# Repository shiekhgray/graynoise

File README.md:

# graynoise
A place for my modular synthesizer designs. Generally openable in [kicad](https://kicad.org/). Or, if you trust me, ship the zipped gerber directories to your favorite PCB house. If you don't have a favorite, I can recommend PCBWay. Parts are generally available from either Tayda or Mouser.

Each directory should be a module, with two (or more) kicad projects. One (or more) should be the actual schematic and logic board(s), the other a faceplate.

## 4mixer
A small, 4hp, 4 channel mono mixer for Eurorack in kicad

## Offset Attenuverter
A 4hp dual attenuverter with offset function, useful for sidechain compression, FM and AM intensity control, and other CV management

## Avalanche
A 4hp? dingus for making white noise by running a zener diode in reverse avalanche mode

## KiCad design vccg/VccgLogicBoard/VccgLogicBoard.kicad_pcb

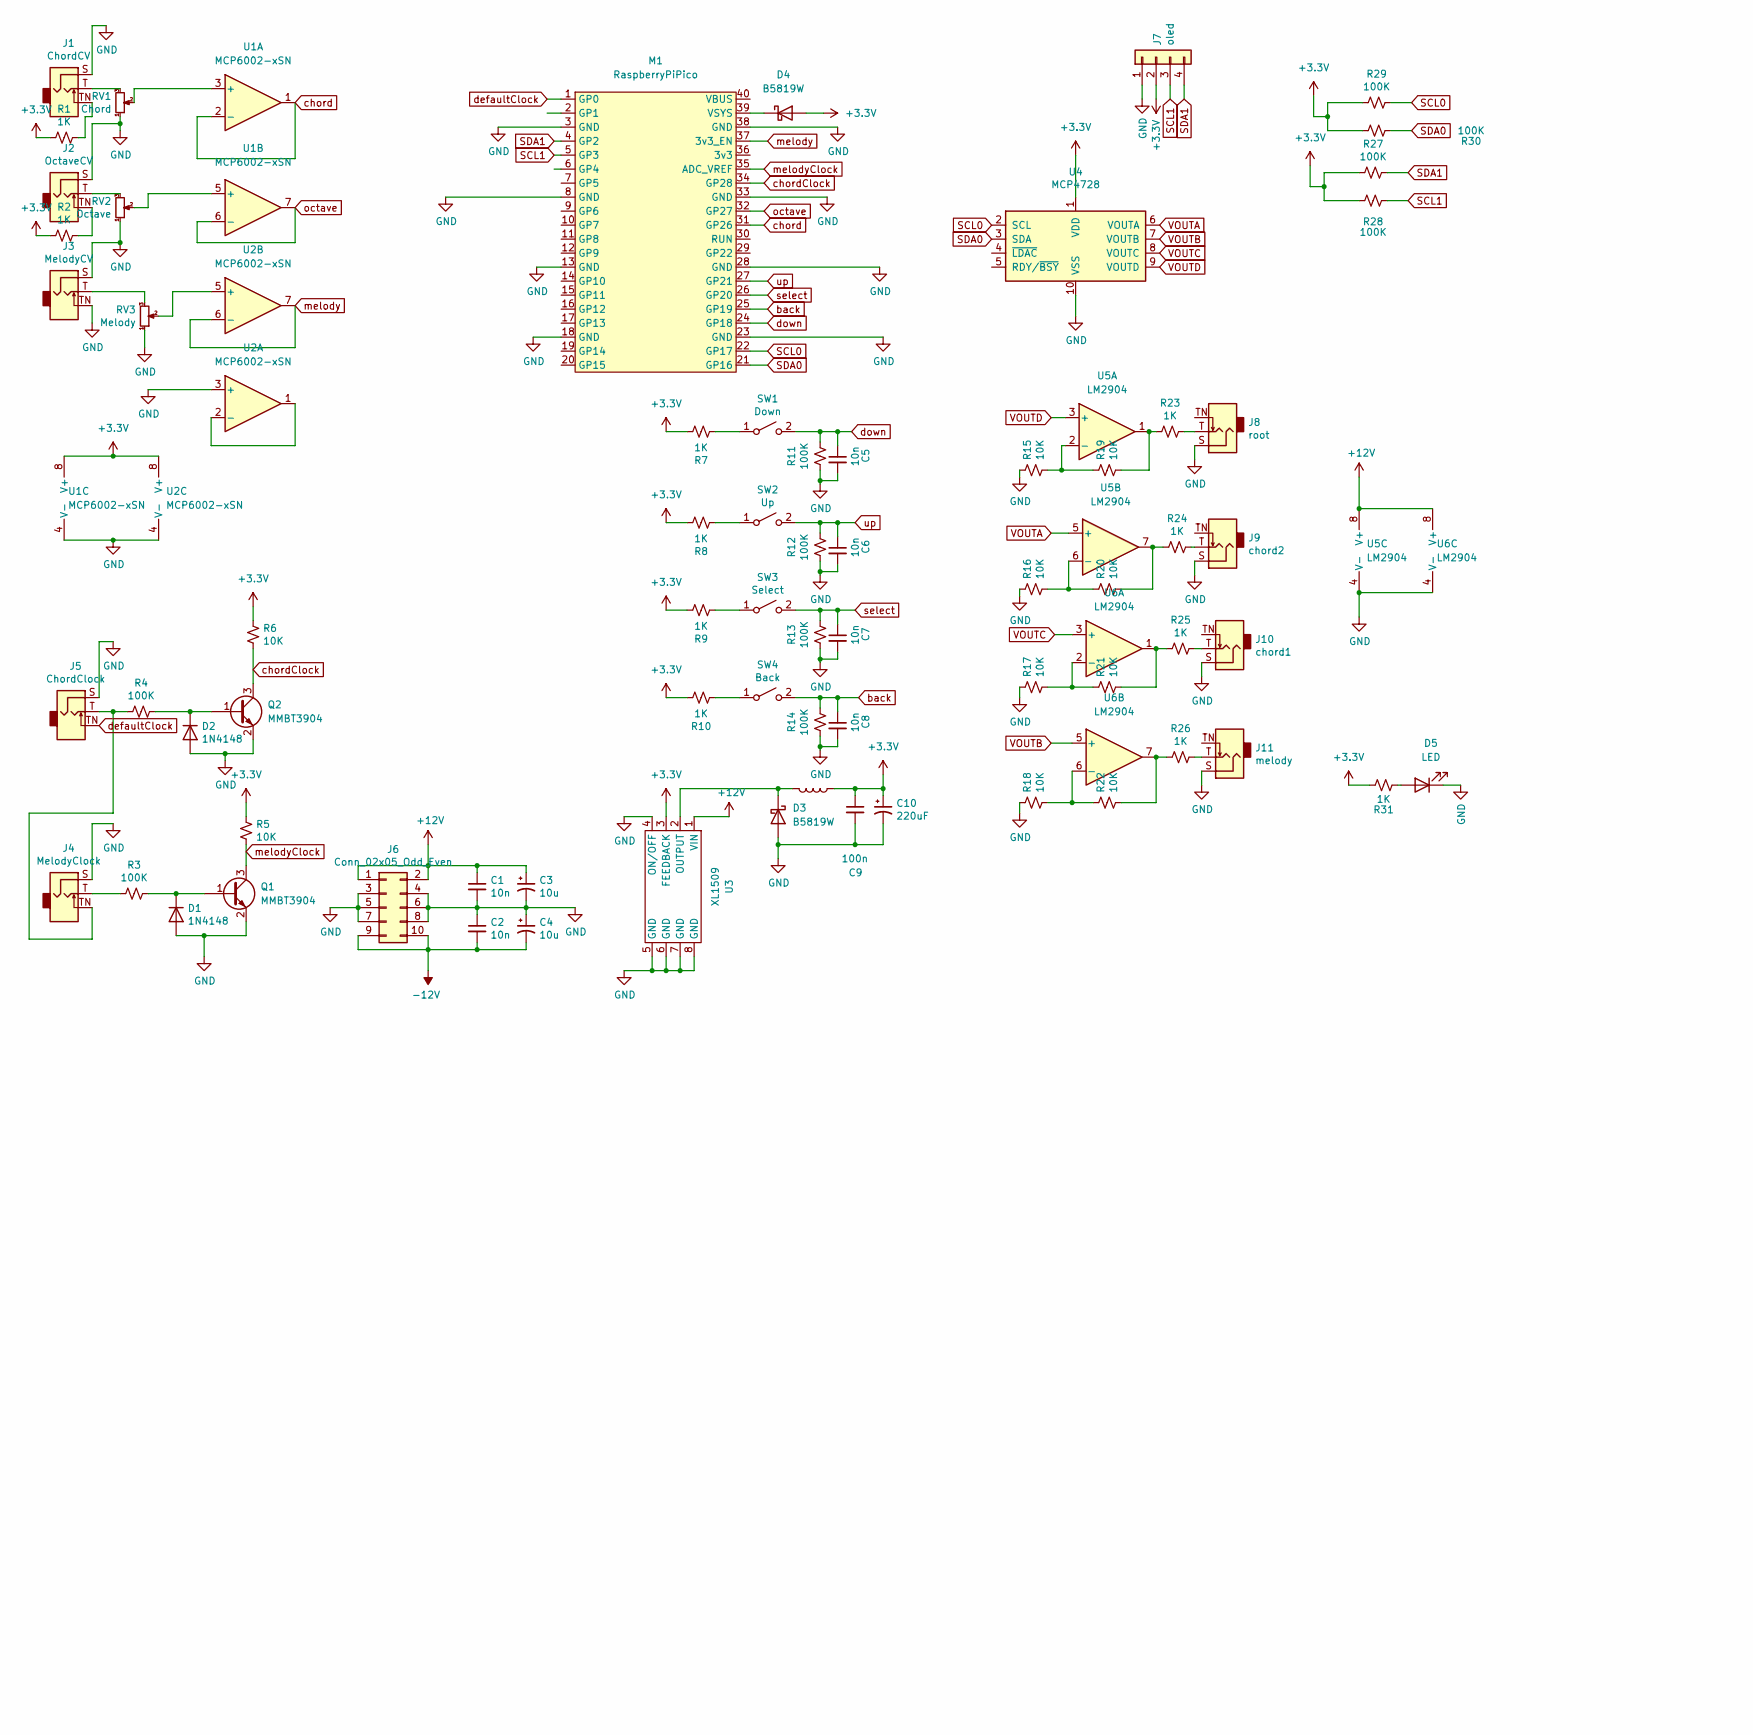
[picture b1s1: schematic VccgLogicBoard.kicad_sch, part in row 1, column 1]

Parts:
C1, C2, C5, C6, C7, C8: 10n; C_0603_1608Metric
C3, C4: 10u; C_0805_2012Metric
C9: 100n; C_0603_1608Metric
C10: 220uF; CP_Elec_6.3x7.7
D1, D2: 1N4148; D_SOD-123
D3, D4: B5819W; D_SOD-123
D5: LED; D_0603_1608Metric
J1: ChordCV; Jack_3.5mm_QingPu_WQP-PJ398SM_Vertical_CircularHoles
J2: OctaveCV; Jack_3.5mm_QingPu_WQP-PJ398SM_Vertical_CircularHoles
J3: MelodyCV; Jack_3.5mm_QingPu_WQP-PJ398SM_Vertical_CircularHoles
J4: MelodyClock; Jack_3.5mm_QingPu_WQP-PJ398SM_Vertical_CircularHoles
J5: ChordClock; Jack_3.5mm_QingPu_WQP-PJ398SM_Vertical_CircularHoles
J6: Conn_02x05_Odd_Even; PinHeader_2x05_P2.54mm_Vertical
J7: oled; PinSocket_1x04_P2.54mm_Vertical
J8: root; Jack_3.5mm_QingPu_WQP-PJ398SM_Vertical_CircularHoles
J9: chord2; Jack_3.5mm_QingPu_WQP-PJ398SM_Vertical_CircularHoles
J10: chord1; Jack_3.5mm_QingPu_WQP-PJ398SM_Vertical_CircularHoles
J11: melody; Jack_3.5mm_QingPu_WQP-PJ398SM_Vertical_CircularHoles
L1: 68uh 2A; Inductor_SMD-CY75-68uh
M1: RaspberryPiPico; Raspberry_Pi_Pico
Q1, Q2: MMBT3904; SOT-23
R1, R2, R7, R8, R9, R10, R23, R24, R25, R26, R31: 1K; R_0603_1608Metric
R3, R4, R11, R12, R13, R14, R27, R28, R29, R30: 100K; R_0603_1608Metric
R5, R6, R15, R16, R17, R18, R19, R20, R21, R22: 10K; R_0603_1608Metric
RV1: Chord; Potentiometer_Alpha_RD901F-40-00D_Single_Vertical_CircularH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
RV2: Octave; Potentiometer_Alpha_RD901F-40-00D_Single_Vertical_CircularH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
RV3: Melody; Potentiometer_Alpha_RD901F-40-00D_Single_Vertical_CircularH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
SW1: Down; SW_PUSH_6mm_H13mm
SW2: Up; SW_PUSH_6mm_H13mm
SW3: Select; SW_PUSH_6mm_H13mm
SW4: Back; SW_PUSH_6mm_H13mm
U1, U2: MCP6002-xSN; SOIC-8_3.9x4.9mm_P1.27mm
U3: XL1509; SOIC-8_3.9x4.9mm_P1.27mm
U4: MCP4728; MSOP-10_3x3mm_P0.5mm
U5, U6: LM2904; SOIC-8_3.9x4.9mm_P1.27mm

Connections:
+3V3: C9.1, C10.1, D4.2 (A), J7.2, L1.1, R1.2, R2.2, R5.2, R6.2, R7.1, R8.1, R9.1, R10.1, R27.2, R28.2, R29.2, R30.2, R31.2, U1.8 (V+), U2.8 (V+), U3.3 (FEEDBACK), U4.1 (VDD)
+12V: C1.1, C3.1, J6.1, J6.2, U3.1 (VIN), U5.8 (V+), U6.8 (V+)
-12V: C2.2, C4.2, J6.9, J6.10
GND: C1.2, C2.1, C3.2, C4.1, C5.2, C6.2, C7.2, C8.2, C9.2, C10.2, D1.2 (A), D2.2 (A), D3.2 (A), D5.1 (K), J1.S, J2.S, J3.S, J3.TN, J4.S, J5.S, J6.3, J6.4, J6.5, J6.6, J6.7, J6.8, J7.1, J8.S, J9.S, J10.S, J11.S, M1.3 (GND), M1.8 (GND), M1.13 (GND), M1.18 (GND), M1.23 (GND), M1.28 (GND), M1.33 (GND), M1.38 (GND), Q1.2 (E), Q2.2 (E), R11.2, R12.2, R13.2, R14.2, R15.2, R16.2, R17.2, R18.2, RV1.1, RV2.1, RV3.1, U1.4 (V-), U2.3 (+), U2.4 (V-), U3.4 (ON/OFF), U3.5 (GND), U3.6 (GND), U3.7 (GND), U3.8 (GND), U4.10 (VSS), U5.4 (V-), U6.4 (V-)
unnamed: D1.1 (K), Q1.1 (B), R3.1
unnamed: D2.1 (K), Q2.1 (B), R4.1
unnamed: D3.1 (K), L1.2, U3.2 (OUTPUT)
unnamed: D4.1 (K), M1.39 (VSYS)
unnamed: D5.2 (A), R31.1
unnamed: J1.T, RV1.3
unnamed: J1.TN, R1.1
unnamed: J2.T, RV2.3
unnamed: J2.TN, R2.1
unnamed: J3.T, RV3.3
unnamed: J4.T, R3.2
unnamed: J4.TN, J5.T, R4.2
unnamed: J8.T, R23.1
unnamed: J9.T, R24.1
unnamed: J10.T, R25.1
unnamed: J11.T, R26.1
unnamed: R7.2, SW1.1 (A)
unnamed: R8.2, SW2.1 (A)
unnamed: R9.2, SW3.1 (A)
unnamed: R10.2, SW4.1 (A)
unnamed: R15.1, R19.2, U5.2 (-)
unnamed: R16.1, R20.2, U5.6 (-)
unnamed: R17.1, R21.2, U6.2 (-)
unnamed: R18.1, R22.2, U6.6 (-)
unnamed: R19.1, R23.2, U5.1
unnamed: R20.1, R24.2, U5.7
unnamed: R21.1, R25.2, U6.1
unnamed: R22.1, R26.2, U6.7
unnamed: RV1.2, U1.3 (+)
unnamed: RV2.2, U1.5 (+)
unnamed: RV3.2, U2.5 (+)
unnamed: U2.1, U2.2 (-)
SCL0: M1.22 (GP17), R29.1, U4.2 (SCL)
SCL1: J7.3, M1.5 (GP3), R28.1
SDA0: M1.21 (GP16), R30.1, U4.3 (SDA)
SDA1: J7.4, M1.4 (GP2), R27.1
VOUTA: U4.6 (VOUTA), U5.5 (+)
VOUTB: U4.7 (VOUTB), U6.5 (+)
VOUTC: U4.8 (VOUTC), U6.3 (+)
VOUTD: U4.9 (VOUTD), U5.3 (+)
back: C8.1, M1.25 (GP19), R14.1, SW4.2 (B)
chord: M1.31 (GP26), U1.1, U1.2 (-)
chordClock: M1.34 (GP28), Q2.3 (C), R6.1
defaultClock: J5.TN, M1.1 (GP0)
down: C5.1, M1.24 (GP18), R11.1, SW1.2 (B)
melody: M1.37 (3v3_EN), U2.6 (-), U2.7
melodyClock: M1.35 (ADC_VREF), Q1.3 (C), R5.1
octave: M1.32 (GP27), U1.6 (-), U1.7
select: C7.1, M1.26 (GP20), R13.1, SW3.2 (B)
up: C6.1, M1.27 (GP21), R12.1, SW2.2 (B)

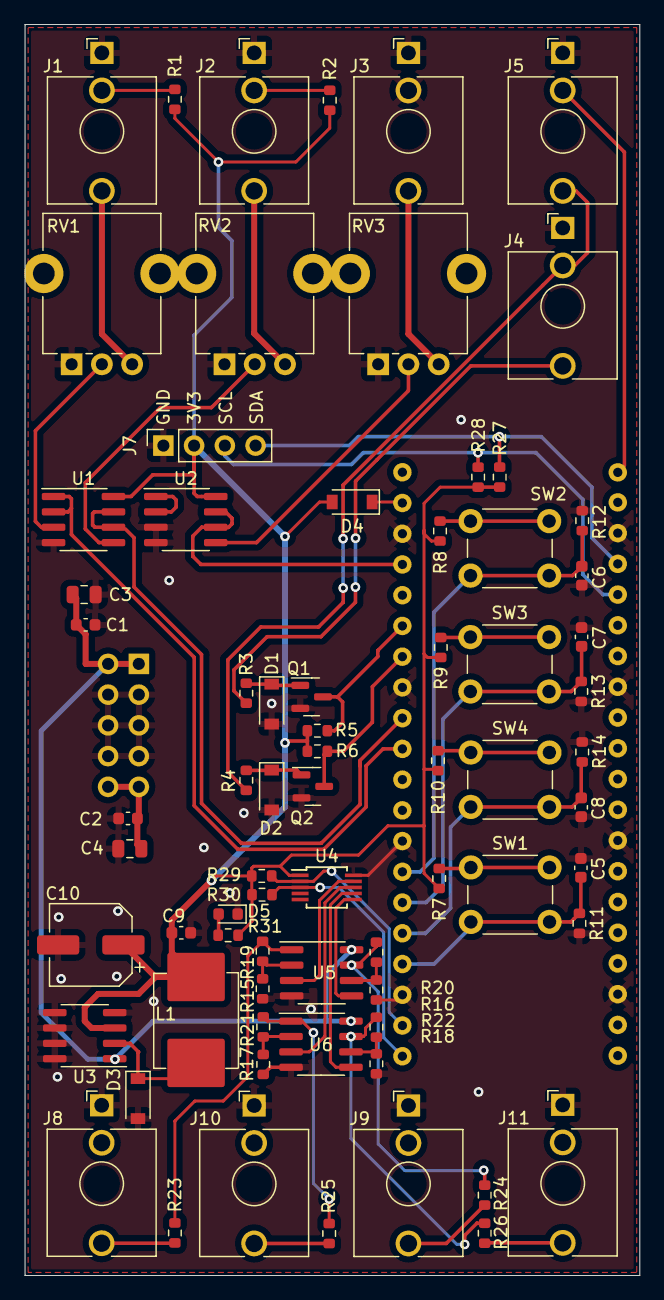
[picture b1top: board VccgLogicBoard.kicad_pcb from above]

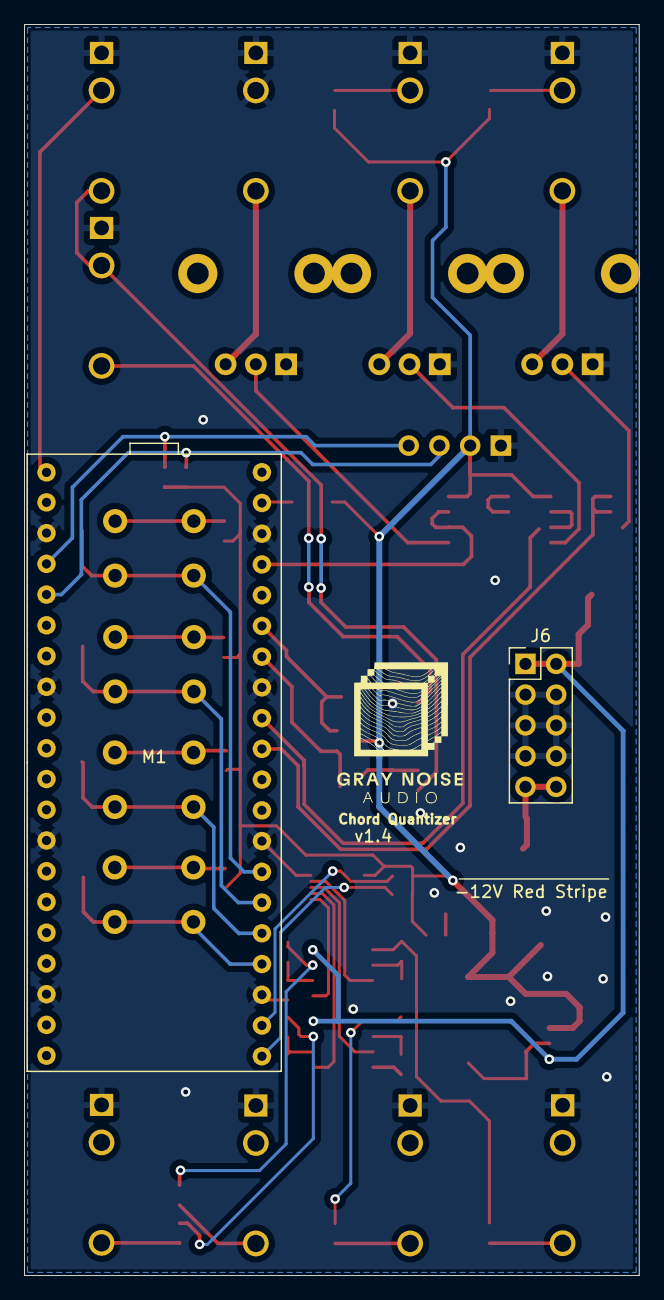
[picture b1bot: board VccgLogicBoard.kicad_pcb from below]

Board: 2 copper layers, 50.8 x 103.4 mm, 74 parts (2 on the bottom side), 54 nets.

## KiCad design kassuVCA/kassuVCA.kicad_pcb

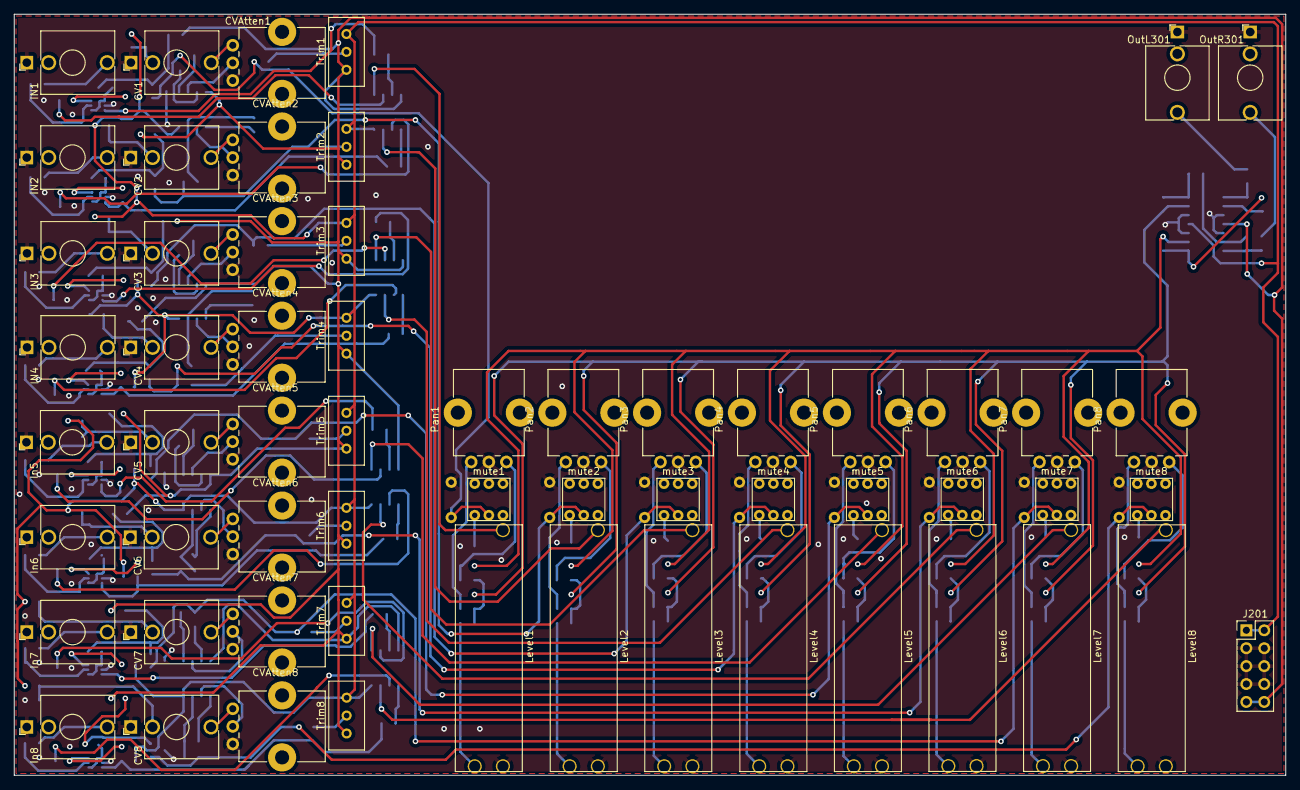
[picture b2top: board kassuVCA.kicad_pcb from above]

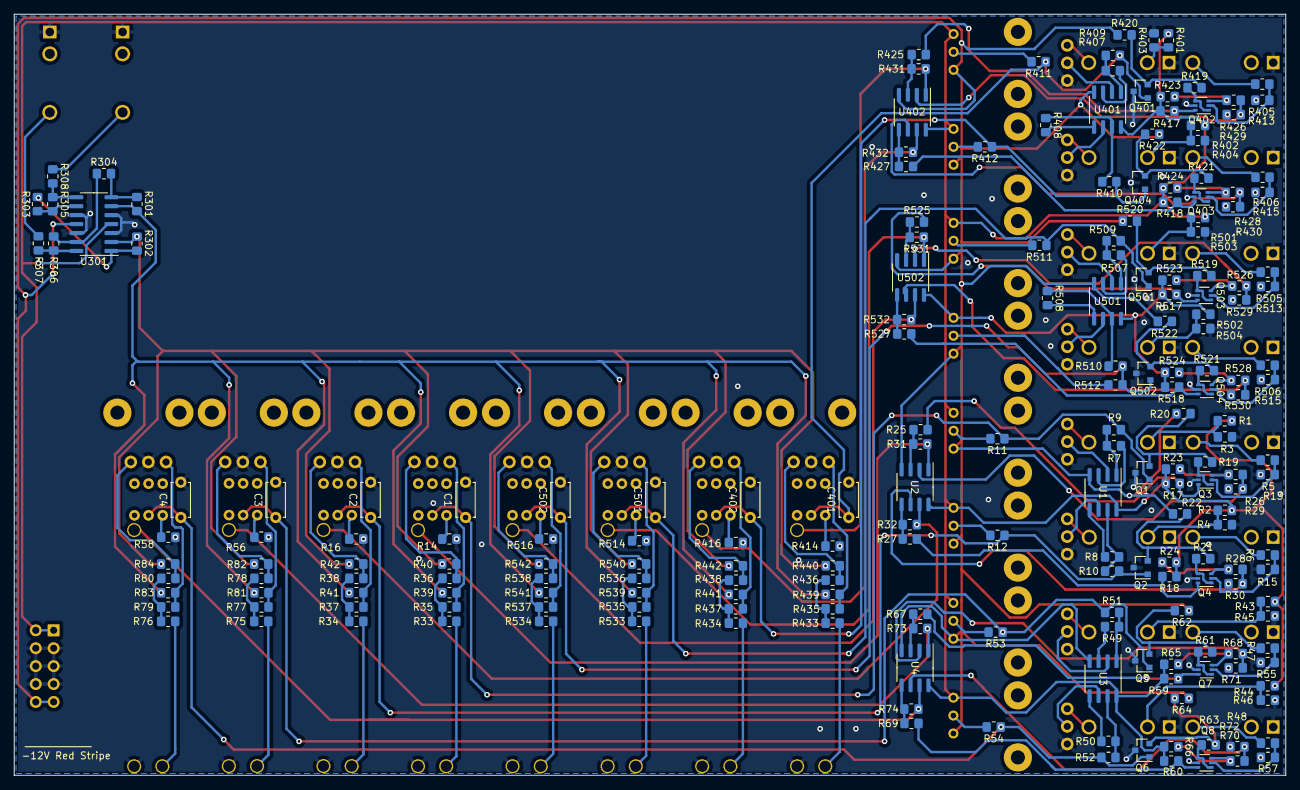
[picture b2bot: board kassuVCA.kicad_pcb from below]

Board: 2 copper layers, 180.3 x 107.9 mm, 268 parts (209 on the bottom side), 181 nets.

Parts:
C1, C2, C3, C4, C401, C402, C501, C502: C; C_Disc_D4.7mm_W2.5mm_P5.00mm
CV1, CV3, CV5, CV6, CV7, CV8: AudioJack2_SwitchT; Jack_3.5mm_QingPu_WQP-PJ398SM_Vertical_CircularHoles
CV2, CV4: AudioJack2_Switch; Jack_3.5mm_QingPu_WQP-PJ398SM_Vertical_CircularHoles
CVAtten1, CVAtten2, CVAtten3, CVAtten4, CVAtten5, CVAtten6, CVAtten7, CVAtten8: 100K; Potentiometer_Alps_RK09K_Single_Vertical
IN1, IN2, IN3, IN4: AudioJack2_SwitchT; Jack_3.5mm_QingPu_WQP-PJ398SM_Vertical_CircularHoles
In5, In6, In7, In8: AudioJack2_SwitchT; Jack_3.5mm_QingPu_WQP-PJ398SM_Vertical_CircularHoles
J201: Conn_02x05_Odd_Even; PinHeader_2x05_P2.54mm_Vertical
Level1, Level2, Level3, Level4, Level5, Level6, Level7, Level8: 100K; A-1623_SlidePot
OutL301: AudioJack2_SwitchT; Jack_3.5mm_QingPu_WQP-PJ398SM_Vertical_CircularHoles
OutR301: AudioJack2_SwitchT; Jack_3.5mm_QingPu_WQP-PJ398SM_Vertical_CircularHoles
Pan1, Pan2, Pan3, Pan4, Pan5, Pan6, Pan7, Pan8: 100K; Potentiometer_Alps_RK09K_Single_Vertical
Q1, Q2, Q5, Q6, Q401, Q404, Q501, Q502: MMBT3904; SOT-23
Q3, Q4, Q7, Q8, Q402, Q403, Q503, Q504: MBT3904DW1; SOT-363_SC-70-6
R1, R2, R5, R6, R29, R30, R31, R32, R33, R34, R43, R44, R47, R48, R71, R72, R73, R74, R75, R76, R401, R402, R405, R406, R429, R430, R431, R432, R433, R434, R501, R502, R505, R506, R529, R530, R531, R532, R533, R534: 220K; R_0805_2012Metric_Pad1.20x1.40mm_HandSolder
R3, R4, R45, R46, R305, R306, R403, R404, R503, R504: 100K; R_0805_2012Metric_Pad1.20x1.40mm_HandSolder
R7, R8, R49, R50, R407, R408, R507, R508: 47K; R_0805_2012Metric_Pad1.20x1.40mm_HandSolder
R9, R10, R11, R12, R19, R21, R35, R36, R37, R38, R39, R40, R41, R42, R51, R52, R53, R54, R61, R63, R77, R78, R79, R80, R81, R82, R83, R84, R409, R410, R411, R412, R419, R421, R435, R436, R437, R438, R439, R440, R441, R442, R509, R510, R511, R512, R519, R521, R535, R536, R537, R538, R539, R540, R541, R542: 22K; R_0805_2012Metric_Pad1.20x1.40mm_HandSolder
R13, R14, R15, R16, R55, R56, R57, R58, R307, R308, R413, R414, R415, R416, R513, R514, R515, R516: 1K; R_0805_2012Metric_Pad1.20x1.40mm_HandSolder
R17, R18, R20, R22, R23, R24, R25, R26, R27, R28, R59, R60, R62, R64, R65, R66, R67, R68, R69, R70, R417, R418, R420, R422, R423, R424, R425, R426, R427, R428, R517, R518, R520, R522, R523, R524, R525, R526, R527, R528: 10K; R_0805_2012Metric_Pad1.20x1.40mm_HandSolder
R301, R302: 39K; R_0805_2012Metric_Pad1.20x1.40mm_HandSolder
R303, R304: 2K; R_0805_2012Metric_Pad1.20x1.40mm_HandSolder
Trim1, Trim2, Trim3, Trim4, Trim5, Trim6, Trim7, Trim8: 100K; Potentiometer_Bourns_3296W_Vertical
U1, U2, U3, U4, U401, U402, U501, U502: TL072; SOIC-8_3.9x4.9mm_P1.27mm
U301: TL074; SOIC-14_3.9x8.7mm_P1.27mm
mute1, mute2, mute3, mute4, mute6, mute8: SW_DPDT_x2; A-330-6mm-dpdt
mute5: mute5; A-330-6mm-dpdt
mute7: mute7; A-330-6mm-dpdt

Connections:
+12V: J201.1, J201.2, R1.1, R2.1, R17.1, R18.1, R23.1, R24.1, R43.1, R44.1, R59.1, R60.1, R65.1, R66.1, R401.1, R402.1, R417.1, R418.1, R423.1, R424.1, R501.1, R502.1, R517.1, R518.1, R523.1, R524.1, Trim1.1, Trim2.1, Trim3.1, Trim4.1, Trim5.1, Trim6.1, Trim7.1, Trim8.1, U1.8 (V+), U2.8 (V+), U3.8 (V+), U4.8 (V+), U301.4 (V+), U401.8 (V+), U402.8 (V+), U501.8 (V+), U502.8 (V+)
-12V: J201.9, J201.10, R20.1, R22.1, R62.1, R64.1, R420.1, R422.1, R520.1, R522.1, Trim1.3, Trim2.3, Trim3.3, Trim4.3, Trim5.3, Trim6.3, Trim7.3, Trim8.3, U1.4 (V-), U2.4 (V-), U3.4 (V-), U4.4 (V-), U301.11 (V-), U401.4 (V-), U402.4 (V-), U501.4 (V-), U502.4 (V-)
GND: C1.2, C2.2, C3.2, C4.2, C401.2, C402.2, C501.2, C502.2, CV1.S, CV2.S, CV3.S, CV4.S, CV5.S, CV6.S, CV7.S, CV8.S, CVAtten1.1, CVAtten2.1, CVAtten3.1, CVAtten4.1, CVAtten5.1, CVAtten6.1, CVAtten7.1, CVAtten8.1, IN1.S, IN2.S, IN3.S, IN4.S, In5.S, In6.S, In7.S, In8.S, J201.3, J201.4, J201.5, J201.6, J201.7, J201.8, Level1.1, Level2.1, Level3.1, Level4.1, Level5.1, Level6.1, Level7.1, Level8.1, OutL301.S, OutR301.S, Pan1.2, Pan2.2, Pan3.2, Pan4.2, Pan5.2, Pan6.2, Pan7.2, Pan8.2, Q1.3 (C), Q2.3 (C), Q3.5 (B2), Q4.5 (B2), Q5.3 (C), Q6.3 (C), Q7.5 (B2), Q8.5 (B2), Q401.3 (C), Q402.5 (B2), Q403.5 (B2), Q404.3 (C), Q501.3 (C), Q502.3 (C), Q503.5 (B2), Q504.5 (B2), R3.2, R4.2, R13.1, R14.1, R15.1, R16.1, R29.1, R30.1, R45.2, R46.2, R55.1, R56.1, R57.1, R58.1, R71.1, R72.1, R403.2, R404.2, R413.1, R414.1, R415.1, R416.1, R429.1, R430.1, R503.2, R504.2, R513.1, R514.1, R515.1, R516.1, R529.1, R530.1, U301.3 (+), U301.5 (+), U301.10 (+), U301.12 (+)
Level1L: R40.2, R42.2, R82.2, R84.2, R302.2, R440.2, R442.2, R540.2, R542.2, U301.2 (-)
Level1R: R39.2, R41.2, R81.2, R83.2, R301.2, R439.2, R441.2, R539.2, R541.2, U301.6 (-)
unnamed: C1.1, Q1.1 (B), R9.1, R11.1, mute5.2 (B)
unnamed: C2.1, Q2.1 (B), R10.1, R12.1, mute6.2 (B)
unnamed: C3.1, Q5.1 (B), R51.1, R53.1, mute7.2 (B)
unnamed: C4.1, Q6.1 (B), R52.1, R54.1, mute8.2 (B)
unnamed: C401.1, Q401.1 (B), R409.1, R411.1, mute1.2 (B)
unnamed: C402.1, Q404.1 (B), R410.1, R412.1, mute2.2 (B)
unnamed: C501.1, Q501.1 (B), R509.1, R511.1, mute3.2 (B)
unnamed: C502.1, Q502.1 (B), R510.1, R512.1, mute4.2 (B)
unnamed: CV1.T, CVAtten1.3
unnamed: CV1.TN, R401.2, R403.1
unnamed: CV2.T, CVAtten2.3
unnamed: CV2.TN, R402.2, R404.1
unnamed: CV3.T, CVAtten3.3
unnamed: CV3.TN, R501.2, R503.1
unnamed: CV4.T, CVAtten4.3
unnamed: CV4.TN, R502.2, R504.1
unnamed: CV5.T, CVAtten5.3
unnamed: CV5.TN, R1.2, R3.1
unnamed: CV6.T, CVAtten6.3
unnamed: CV6.TN, R2.2, R4.1
unnamed: CV7.T, CVAtten7.3
unnamed: CV7.TN, R43.2, R45.1
unnamed: CV8.T, CVAtten8.3
unnamed: CV8.TN, R44.2, R46.1
unnamed: CVAtten1.2, U401.2 (-)
unnamed: CVAtten2.2, U401.6 (-)
unnamed: CVAtten3.2, U501.2 (-)
unnamed: CVAtten4.2, U501.6 (-)
unnamed: CVAtten5.2, U1.2 (-)
unnamed: CVAtten6.2, U1.6 (-)
unnamed: CVAtten7.2, U3.2 (-)
unnamed: CVAtten8.2, U3.6 (-)
unnamed: IN1.T, R405.2
unnamed: IN2.T, R406.2
unnamed: IN3.T, R505.2
unnamed: IN4.T, R506.2
unnamed: In5.T, R5.2
unnamed: In6.T, R6.2
unnamed: In7.T, R47.2
unnamed: In8.T, R48.2
unnamed: Level1.2, R433.1
unnamed: Level1.3, R431.1, U402.1
unnamed: Level2.2, R434.1
unnamed: Level2.3, R432.1, U402.7
unnamed: Level3.2, R533.1
unnamed: Level3.3, R531.1, U502.1
unnamed: Level4.2, R534.1
unnamed: Level4.3, R532.1, U502.7
unnamed: Level5.2, R33.1
unnamed: Level5.3, R31.1, U2.1
unnamed: Level6.2, R34.1
unnamed: Level6.3, R32.1, U2.7
unnamed: Level7.2, R75.1
unnamed: Level7.3, R73.1, U4.1
unnamed: Level8.2, R76.1
unnamed: Level8.3, R74.1, U4.7
unnamed: OutL301.T, R308.1
unnamed: OutR301.T, R307.1
unnamed: Pan1.1, R436.2, R440.1
unnamed: Pan1.3, R435.2, R439.1
unnamed: Pan2.1, R438.2, R442.1
unnamed: Pan2.3, R437.2, R441.1
unnamed: Pan3.1, R536.2, R540.1
unnamed: Pan3.3, R535.2, R539.1
unnamed: Pan4.1, R538.2, R542.1
unnamed: Pan4.3, R537.2, R541.1
unnamed: Pan5.1, R36.2, R40.1
unnamed: Pan5.3, R35.2, R39.1
unnamed: Pan6.1, R38.2, R42.1
unnamed: Pan6.3, R37.2, R41.1
unnamed: Pan7.1, R78.2, R82.1
unnamed: Pan7.3, R77.2, R81.1
unnamed: Pan8.1, R80.2, R84.1
unnamed: Pan8.3, R79.2, R83.1
unnamed: Q1.2 (E), R19.2, R20.2
unnamed: Q2.2 (E), R21.2, R22.2
unnamed: Q3.1 (E1), Q3.4 (E2), R19.1
unnamed: Q3.2 (B1), R5.1, R13.2
unnamed: Q3.3 (C2), R23.2, R26.2
unnamed: Q3.6 (C1), R17.2, R25.2
unnamed: Q4.1 (E1), Q4.4 (E2), R21.1
unnamed: Q4.2 (B1), R6.1, R15.2
unnamed: Q4.3 (C2), R24.2, R28.2
unnamed: Q4.6 (C1), R18.2, R27.2
unnamed: Q5.2 (E), R61.2, R62.2
unnamed: Q6.2 (E), R63.2, R64.2
unnamed: Q7.1 (E1), Q7.4 (E2), R61.1
unnamed: Q7.2 (B1), R47.1, R55.2
unnamed: Q7.3 (C2), R65.2, R68.2
unnamed: Q7.6 (C1), R59.2, R67.2
unnamed: Q8.1 (E1), Q8.4 (E2), R63.1
unnamed: Q8.2 (B1), R48.1, R57.2
unnamed: Q8.3 (C2), R66.2, R70.2
unnamed: Q8.6 (C1), R60.2, R69.2
unnamed: Q401.2 (E), R419.2, R420.2
unnamed: Q402.1 (E1), Q402.4 (E2), R419.1
unnamed: Q402.2 (B1), R405.1, R413.2
unnamed: Q402.3 (C2), R423.2, R426.2
unnamed: Q402.6 (C1), R417.2, R425.2
unnamed: Q403.1 (E1), Q403.4 (E2), R421.1
unnamed: Q403.2 (B1), R406.1, R415.2
unnamed: Q403.3 (C2), R424.2, R428.2
unnamed: Q403.6 (C1), R418.2, R427.2
unnamed: Q404.2 (E), R421.2, R422.2
unnamed: Q501.2 (E), R519.2, R520.2
unnamed: Q502.2 (E), R521.2, R522.2
unnamed: Q503.1 (E1), Q503.4 (E2), R519.1
unnamed: Q503.2 (B1), R505.1, R513.2
unnamed: Q503.3 (C2), R523.2, R526.2
unnamed: Q503.6 (C1), R517.2, R525.2
unnamed: Q504.1 (E1), Q504.4 (E2), R521.1
unnamed: Q504.2 (B1), R506.1, R515.2
unnamed: Q504.3 (C2), R524.2, R528.2
unnamed: Q504.6 (C1), R518.2, R527.2
unnamed: R7.1, R9.2, U1.1
unnamed: R7.2, U1.3 (+)
unnamed: R8.2, U1.5 (+)
unnamed: R8.1, R10.2, U1.7
unnamed: R11.2, Trim5.2
unnamed: R12.2, Trim6.2
unnamed: R14.2, mute5.1 (A)
unnamed: R16.2, mute6.1 (A)
unnamed: R25.1, R31.2, U2.3 (+)
unnamed: R26.1, R29.2, U2.2 (-)
unnamed: R27.1, R32.2, U2.5 (+)
unnamed: R28.1, R30.2, U2.6 (-)
unnamed: R33.2, R35.1, R36.1
unnamed: R34.2, R37.1, R38.1
unnamed: R49.1, R51.2, U3.1
unnamed: R49.2, U3.3 (+)
unnamed: R50.1, R52.2, U3.7
unnamed: R50.2, U3.5 (+)
unnamed: R53.2, Trim7.2
unnamed: R54.2, Trim8.2
unnamed: R56.2, mute7.1 (A)
unnamed: R58.2, mute8.1 (A)
unnamed: R67.1, R73.2, U4.3 (+)
unnamed: R68.1, R71.2, U4.2 (-)
unnamed: R69.1, R74.2, U4.5 (+)
unnamed: R70.1, R72.2, U4.6 (-)
unnamed: R75.2, R77.1, R78.1
unnamed: R76.2, R79.1, R80.1
unnamed: R301.1, R304.2, U301.7
unnamed: R302.1, R303.2, U301.1
unnamed: R303.1, R305.2, U301.9 (-)
unnamed: R304.1, R306.2, U301.13 (-)
unnamed: R305.1, R308.2, U301.8
unnamed: R306.1, R307.2, U301.14
unnamed: R407.1, R409.2, U401.1
unnamed: R407.2, U401.3 (+)
unnamed: R408.1, R410.2, U401.7
unnamed: R408.2, U401.5 (+)
unnamed: R411.2, Trim1.2
unnamed: R412.2, Trim2.2
unnamed: R414.2, mute1.1 (A)
unnamed: R416.2, mute2.1 (A)
unnamed: R425.1, R431.2, U402.3 (+)
unnamed: R426.1, R429.2, U402.2 (-)
unnamed: R427.1, R432.2, U402.5 (+)
unnamed: R428.1, R430.2, U402.6 (-)
unnamed: R433.2, R435.1, R436.1
unnamed: R434.2, R437.1, R438.1
unnamed: R507.1, R509.2, U501.1
unnamed: R507.2, U501.3 (+)
unnamed: R508.1, R510.2, U501.7
unnamed: R508.2, U501.5 (+)
unnamed: R511.2, Trim3.2
unnamed: R512.2, Trim4.2
unnamed: R514.2, mute3.1 (A)
unnamed: R516.2, mute4.1 (A)
unnamed: R525.1, R531.2, U502.3 (+)
unnamed: R526.1, R529.2, U502.2 (-)
unnamed: R527.1, R532.2, U502.5 (+)
unnamed: R528.1, R530.2, U502.6 (-)
unnamed: R533.2, R535.1, R536.1
unnamed: R534.2, R537.1, R538.1

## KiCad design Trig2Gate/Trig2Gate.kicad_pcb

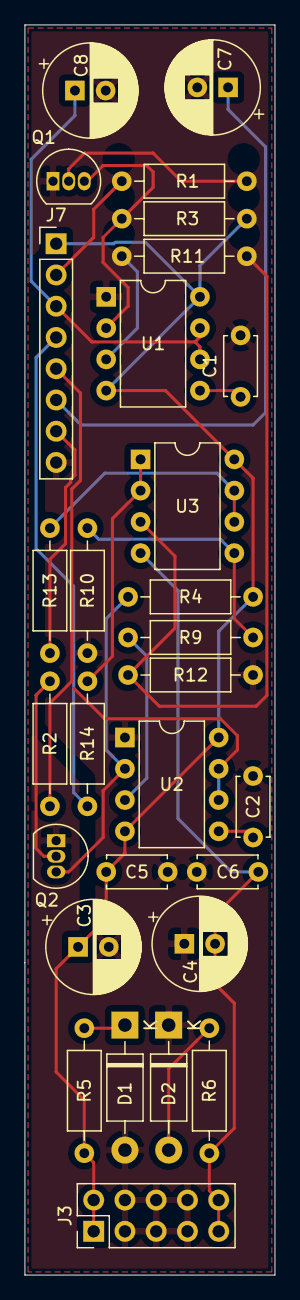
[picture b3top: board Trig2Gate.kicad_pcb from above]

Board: 2 copper layers, 20.3 x 101.6 mm, 29 parts (0 on the bottom side), 23 nets.

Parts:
C1, C2, C5, C6: 100n; C_Disc_D4.7mm_W2.5mm_P5.00mm
C3, C4, C7, C8: 100u; CP_Radial_D7.5mm_P2.50mm
D1, D2: 1N4001; D_DO-41_SOD81_P10.16mm_Horizontal
J3: Conn_02x05_Odd_Even; PinHeader_2x05_P2.54mm_Vertical
J7: Conn_01x08_Male; PinHeader_1x08_P2.54mm_Vertical
Q1, Q2: 2N3904; TO-92_Inline
R1, R2: 10K; R_Axial_DIN0207_L6.3mm_D2.5mm_P10.16mm_Horizontal
R3, R4, R9, R10, R11, R12: 100K; R_Axial_DIN0207_L6.3mm_D2.5mm_P10.16mm_Horizontal
R5, R6: 68; R_Axial_DIN0207_L6.3mm_D2.5mm_P10.16mm_Horizontal
R13, R14: 2K2; R_Axial_DIN0207_L6.3mm_D2.5mm_P10.16mm_Horizontal
U1, U2: NE555P; DIP-8_W7.62mm
U3: TL072; DIP-8_W7.62mm

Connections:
+12V: C3.1, C5.1, J3.1, J3.2, J7.1, R3.2, R4.2, R5.2, U1.4, U1.8, U2.4, U2.8, U3.8
-12V: C4.2, C6.2, J3.9, J3.10, R6.2, U3.4
G1: J7.4, R14.2
G2: J7.7, R13.2
GND: C1.2, C2.2, C3.2, C4.1, C5.2, C6.1, C7.2, C8.2, D1.2, D2.1, J3.3, J3.4, J3.5, J3.6, J3.7, J3.8, J7.8, Q1.1, Q2.1, R10.2, R12.2, U1.1, U2.1
unnamed: C1.1, U1.5
unnamed: C2.1, U2.5
unnamed: D1.1, R5.1
unnamed: D2.2, R6.1
unnamed: Q1.2, R1.1
unnamed: Q1.3, R3.1, U1.2
unnamed: Q2.2, R2.1
unnamed: Q2.3, R4.1, U2.2
unnamed: R9.1, U2.3
unnamed: R9.2, R10.1, U3.5
unnamed: R11.1, U1.3
unnamed: R11.2, R12.1, U3.3
unnamed: R13.1, U3.6, U3.7
unnamed: R14.1, U3.1, U3.2
T1: J7.2, R1.2
T2: J7.5, R2.2
V1: C8.1, J7.3, U1.6, U1.7
V2: C7.1, J7.6, U2.6, U2.7

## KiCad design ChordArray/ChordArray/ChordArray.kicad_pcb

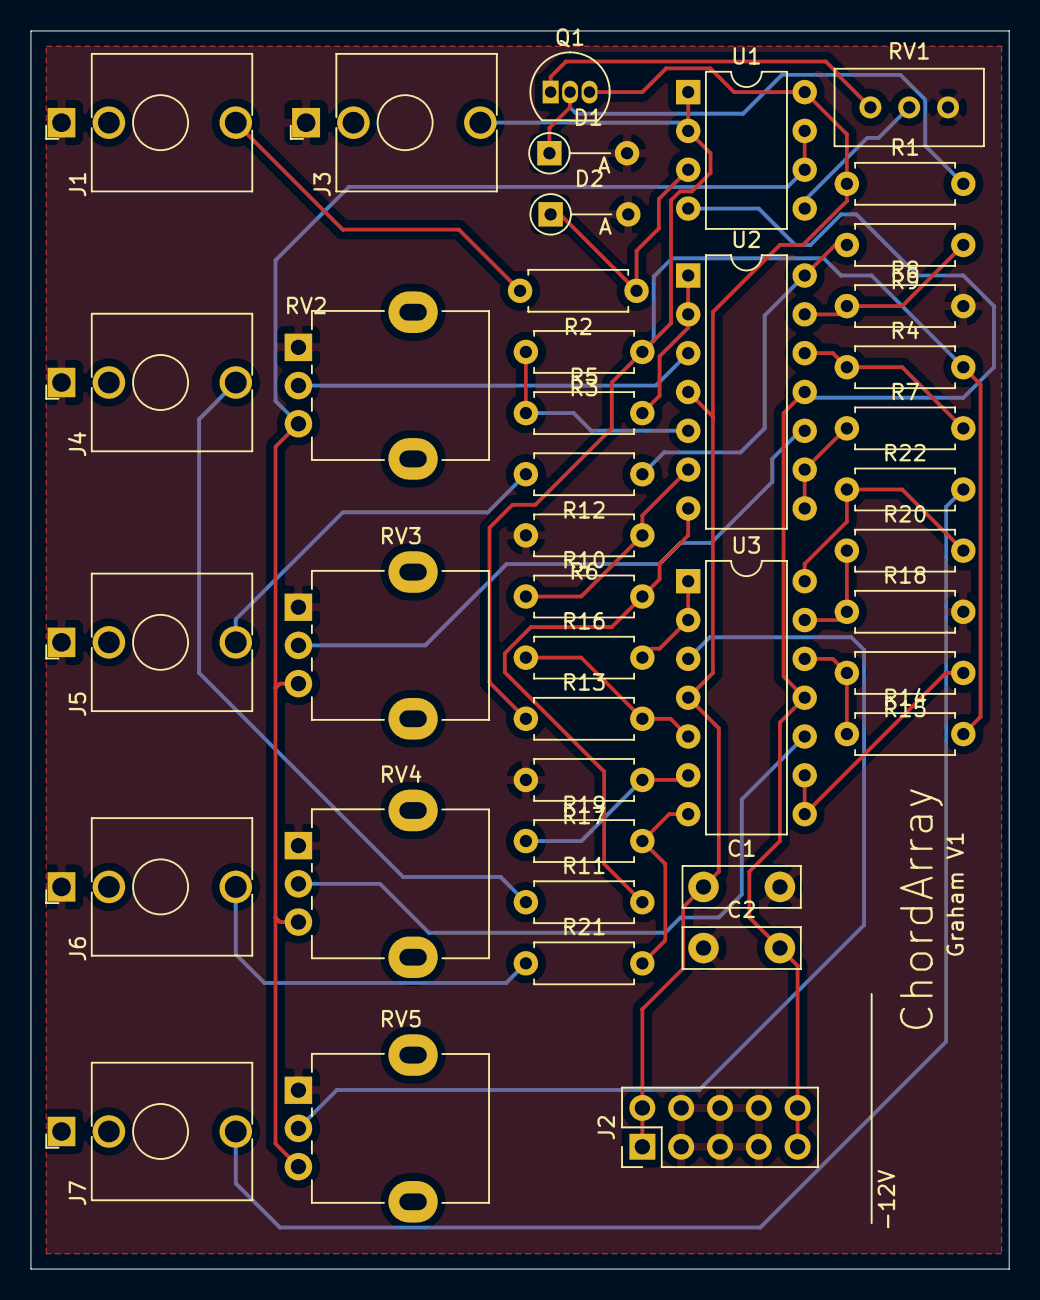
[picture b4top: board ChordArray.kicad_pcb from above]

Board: 2 copper layers, 64.0 x 81.0 mm, 42 parts (0 on the bottom side), 34 nets.

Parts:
C1, C2: 100n; C_Disc_D7.5mm_W2.5mm_P5.00mm
D1: 1n5226B; D_DO-35_SOD27_P5.08mm_Vertical_AnodeUp
D2: 1n5233B; D_DO-35_SOD27_P5.08mm_Vertical_AnodeUp
J1: CV_IN; Jack_3.5mm_QingPu_WQP-PJ398SM_Vertical_CircularHoles
J2: Conn_02x05_Odd_Even; PinHeader_2x05_P2.54mm_Vertical
J3: BUFFERED_OUT; Jack_3.5mm_QingPu_WQP-PJ398SM_Vertical_CircularHoles
J4: OFFSET1; Jack_3.5mm_QingPu_WQP-PJ398SM_Vertical_CircularHoles
J5: OFFSET2; Jack_3.5mm_QingPu_WQP-PJ398SM_Vertical_CircularHoles
J6: OFFSET3; Jack_3.5mm_QingPu_WQP-PJ398SM_Vertical_CircularHoles
J7: OFFSET4; Jack_3.5mm_QingPu_WQP-PJ398SM_Vertical_CircularHoles
Q1: 2N3904; TO-92_Inline
R1, R2: 10K; R_Axial_DIN0207_L6.3mm_D2.5mm_P7.62mm_Horizontal
R3, R4, R5, R6, R7, R8, R9, R10, R13, R14, R15, R16, R17, R18, R19, R20: 100K; R_Axial_DIN0207_L6.3mm_D2.5mm_P7.62mm_Horizontal
R11, R12, R21, R22: 1K; R_Axial_DIN0207_L6.3mm_D2.5mm_P7.62mm_Horizontal
RV1: 100K; Potentiometer_Bourns_3296W_Vertical
RV2, RV3, RV4, RV5: 100K; Potentiometer_Alpha_RD901F-40-00D_Single_Vertical
U1: TL072; DIP-8_W7.62mm
U2, U3: TL074; DIP-14_W7.62mm

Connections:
1V: RV2.3, RV3.3, RV4.3, RV5.3, U1.6, U1.7
+12V: C1.1, J2.1, J2.2, Q1.3, R1.1, U1.8, U2.4, U3.4
-12V: C2.2, J2.9, J2.10, U1.4, U2.11, U3.11
CV: J3.T, R3.1, R4.2, R13.1, R14.2, U1.1, U1.2
GND: C1.2, C2.1, D1.2, D2.2, J1.S, J2.3, J2.4, J2.5, J2.6, J2.7, J2.8, J3.S, J4.S, J5.S, J6.S, R6.2, R8.2, R17.2, R18.2, RV1.1, RV2.1, RV3.1, RV4.1, RV5.1
unnamed: D1.1, Q1.2, R1.2
unnamed: D2.1, R2.1, U1.3
unnamed: J1.T, R2.2
unnamed: J4.T, R11.1
unnamed: J5.T, R12.2
unnamed: J6.T, R21.1
unnamed: J7.T, R22.2
unnamed: Q1.1, RV1.3
unnamed: R3.2, R5.1, U2.5
unnamed: R4.1, R7.2, U2.12
unnamed: R5.2, U2.1, U2.2
unnamed: R7.1, U2.8, U2.9
unnamed: R8.1, R9.1, U2.13
unnamed: R6.1, R10.1, U2.6
unnamed: R10.2, R11.2, U2.7
unnamed: R9.2, R12.1, U2.14
unnamed: R13.2, R16.1, U3.5
unnamed: R14.1, R15.2, U3.12
unnamed: R15.1, U3.8, U3.9
unnamed: R16.2, U3.1, U3.2
unnamed: R17.1, R19.1, U3.6
unnamed: R18.1, R20.1, U3.13
unnamed: R19.2, R21.2, U3.7
unnamed: R20.2, R22.1, U3.14
unnamed: RV1.2, U1.5
unnamed: RV2.2, U2.3
unnamed: RV3.2, U2.10
unnamed: RV4.2, U3.10
unnamed: RV5.2, U3.3
